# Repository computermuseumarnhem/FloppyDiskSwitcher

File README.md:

# FloppyDiskSwitcher
Select 1 of 4 floppy drives connected to a single controller

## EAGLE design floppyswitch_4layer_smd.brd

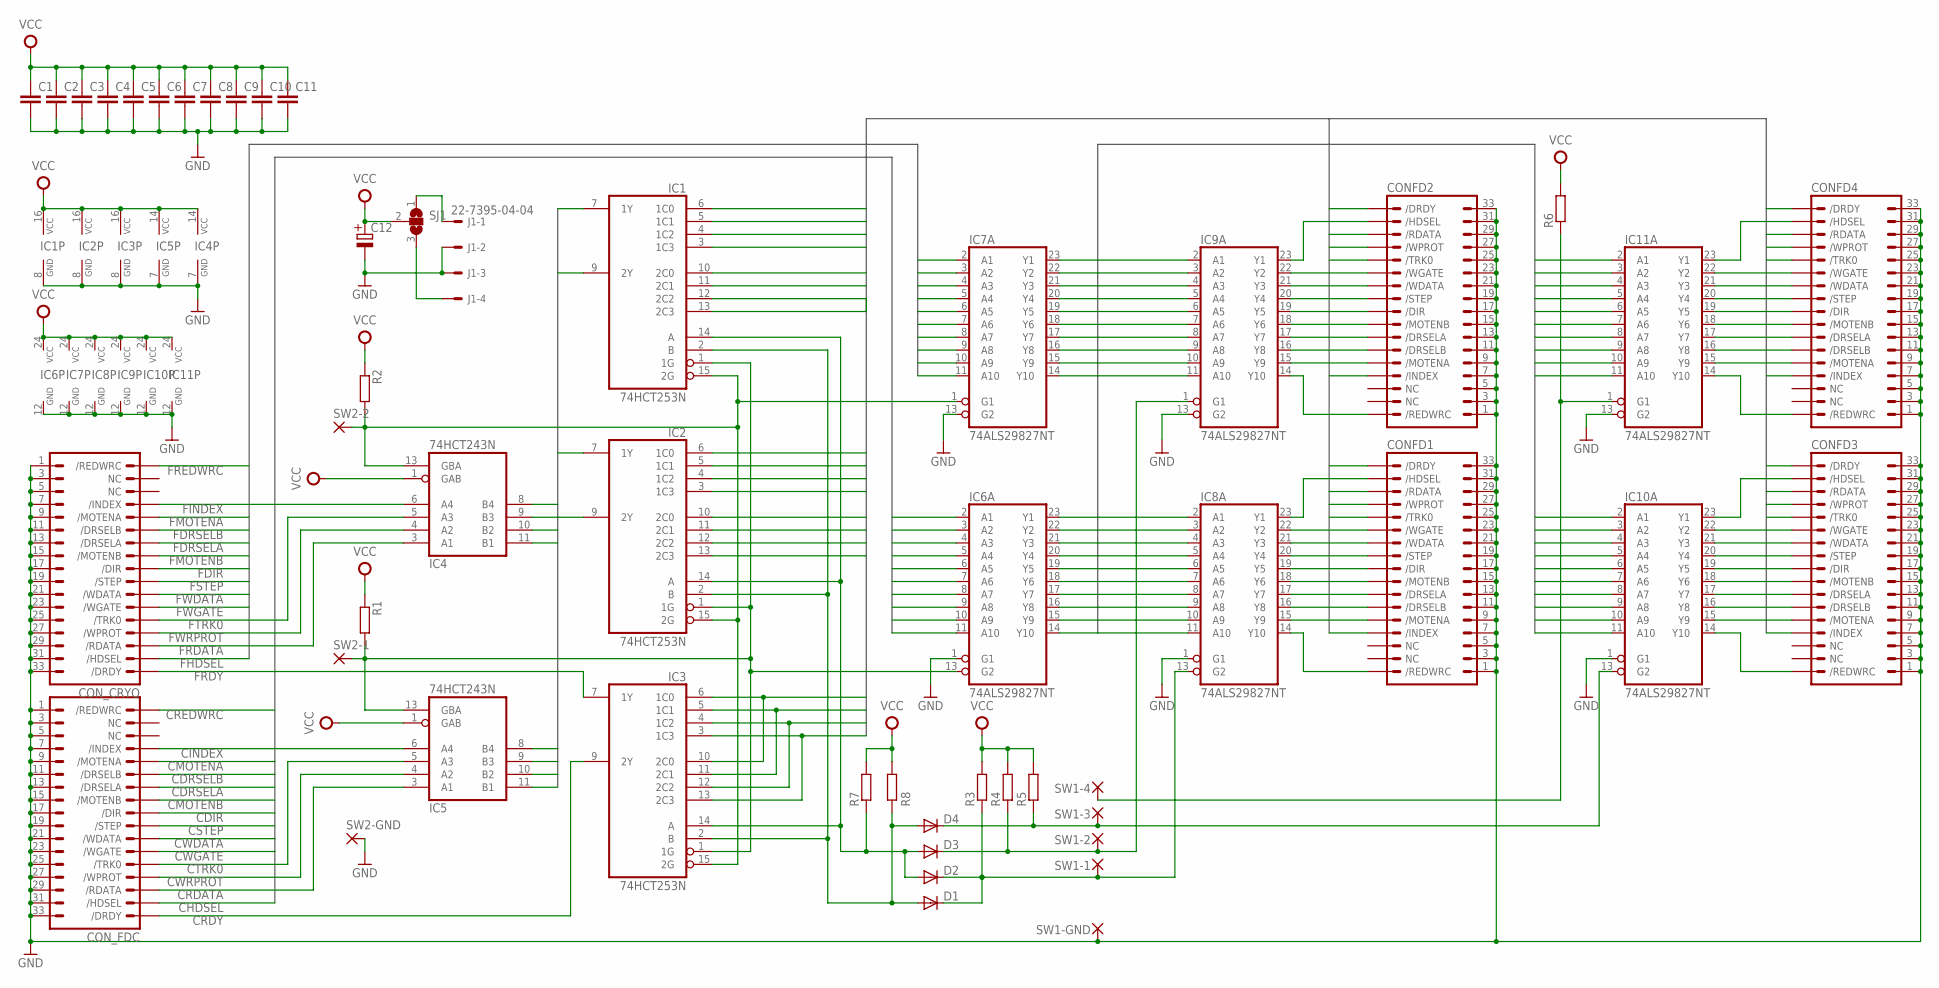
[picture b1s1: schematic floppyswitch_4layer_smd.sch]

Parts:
C1, C5, C6, C7, C8, C9, C10: C-EU075-032X103; C075-032X103
C2: C-EU025-025X050; C025-025X050
C3, C4, C11: C-EU050-025X075; C050-025X075
C12: CPOL-EUE2.5-6; E2,5-6
CONFD1, CONFD2, CONFD3, CONFD4: FDC342X17; 2X17
CON_CRYO: FDC342X17; 2X17
CON_FDC: FDC342X17; 2X17
D1, D2, D3, D4: 1N4148-7; DO35-7
IC1, IC2, IC3: 74HCT253N; DIL16
IC4, IC5: 74HCT243N; DIL14
IC6, IC7, IC8, IC9, IC10, IC11: 74ALS29827NT; SO24W
J1: 22-7395-04-04; 7395-04
R1, R2, R3, R4, R5, R6, R7, R8: R-EU0207/10; 0207/10
SJ1: SJ2W; SJ_2
SW1-1, SW1-2, SW1-3, SW1-4, SW1-GND, SW2-1, SW2-2, SW2-GND: WIREPAD1,6/0,8; 1,6/0,8

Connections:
BUS1: IC6.14 (Y10), IC7.14 (Y10), IC8.11 (A10), IC9.11 (A10), IC10.11 (A10), IC11.11 (A10)
BUS2: IC6.15 (Y9), IC7.15 (Y9), IC8.10 (A9), IC9.10 (A9), IC10.10 (A9), IC11.10 (A9)
BUS3: IC6.16 (Y8), IC7.16 (Y8), IC8.9 (A8), IC9.9 (A8), IC10.9 (A8), IC11.9 (A8)
BUS4: IC6.17 (Y7), IC7.17 (Y7), IC8.8 (A7), IC9.8 (A7), IC10.8 (A7), IC11.8 (A7)
BUS5: IC6.18 (Y6), IC7.18 (Y6), IC8.7 (A6), IC9.7 (A6), IC10.7 (A6), IC11.7 (A6)
BUS6: IC6.19 (Y5), IC7.19 (Y5), IC8.6 (A5), IC9.6 (A5), IC10.6 (A5), IC11.6 (A5)
BUS7: IC6.20 (Y4), IC7.20 (Y4), IC8.5 (A4), IC9.5 (A4), IC10.5 (A4), IC11.5 (A4)
BUS8: IC6.21 (Y3), IC7.21 (Y3), IC8.4 (A3), IC9.4 (A3), IC10.4 (A3), IC11.4 (A3)
BUS9: IC6.22 (Y2), IC7.22 (Y2), IC8.3 (A2), IC9.3 (A2), IC10.3 (A2), IC11.3 (A2)
BUS10: IC6.23 (Y1), IC7.23 (Y1), IC8.2 (A1), IC9.2 (A1), IC10.2 (A1), IC11.2 (A1)
CDIR: CON_FDC.18 (/DIR), IC6.6 (A5)
CDRSELA: CON_FDC.14 (/DRSELA), IC6.8 (A7)
CDRSELB: CON_FDC.12 (/DRSELB), IC6.9 (A8)
CHDSEL: CON_FDC.32 (/HDSEL), IC6.2 (A1)
CINDEX: CON_FDC.8 (/INDEX), IC5.6 (A4)
CMOTENA: CON_FDC.10 (/MOTENA), IC6.10 (A9)
CMOTENB: CON_FDC.16 (/MOTENB), IC6.7 (A6)
CRDATA: CON_FDC.30 (/RDATA), IC5.3 (A1)
CRDY: CON_FDC.34 (/DRDY), IC3.9 (2Y)
CREDWRC: CON_FDC.2 (/REDWRC), IC6.11 (A10)
CSTEP: CON_FDC.20 (/STEP), IC6.5 (A4)
CTRK0: CON_FDC.26 (/TRK0), IC5.5 (A3)
CWDATA: CON_FDC.22 (/WDATA), IC6.4 (A3)
CWGATE: CON_FDC.24 (/WGATE), IC6.3 (A2)
CWRPROT: CON_FDC.28 (/WPROT), IC5.4 (A2)
FDIR: CON_CRYO.18 (/DIR), IC7.6 (A5)
FDRSELA: CON_CRYO.14 (/DRSELA), IC7.8 (A7)
FDRSELB: CON_CRYO.12 (/DRSELB), IC7.9 (A8)
FHDSEL: CON_CRYO.32 (/HDSEL), IC7.2 (A1)
FINDEX: CON_CRYO.8 (/INDEX), IC4.6 (A4)
FMOTENA: CON_CRYO.10 (/MOTENA), IC7.10 (A9)
FMOTENB: CON_CRYO.16 (/MOTENB), IC7.7 (A6)
FRDATA: CON_CRYO.30 (/RDATA), IC4.3 (A1)
FRDY: CON_CRYO.34 (/DRDY), IC3.7 (1Y)
FREDWRC: CON_CRYO.2 (/REDWRC), IC7.11 (A10)
FSTEP: CON_CRYO.20 (/STEP), IC7.5 (A4)
FTRK0: CON_CRYO.26 (/TRK0), IC4.5 (A3)
FWDATA: CON_CRYO.22 (/WDATA), IC7.4 (A3)
FWGATE: CON_CRYO.24 (/WGATE), IC7.3 (A2)
FWRPROT: CON_CRYO.28 (/WPROT), IC4.4 (A2)
GND: C1.2, C2.2, C3.2, C4.2, C5.2, C6.2, C7.2, C8.2, C9.2, C10.2, C11.2, C12.-, CONFD1.1, CONFD1.3, CONFD1.5, CONFD1.7, CONFD1.9, CONFD1.11, CONFD1.13, CONFD1.15, CONFD1.17, CONFD1.19, CONFD1.21, CONFD1.23, CONFD1.25, CONFD1.27, CONFD1.29, CONFD1.31, CONFD1.33, CONFD2.1, CONFD2.3, CONFD2.5, CONFD2.7, CONFD2.9, CONFD2.11, CONFD2.13, CONFD2.15, CONFD2.17, CONFD2.19, CONFD2.21, CONFD2.23, CONFD2.25, CONFD2.27, CONFD2.29, CONFD2.31, CONFD2.33, CONFD3.1, CONFD3.3, CONFD3.5, CONFD3.7, CONFD3.9, CONFD3.11, CONFD3.13, CONFD3.15, CONFD3.17, CONFD3.19, CONFD3.21, CONFD3.23, CONFD3.25, CONFD3.27, CONFD3.29, CONFD3.31, CONFD3.33, CONFD4.1, CONFD4.3, CONFD4.5, CONFD4.7, CONFD4.9, CONFD4.11, CONFD4.13, CONFD4.15, CONFD4.17, CONFD4.19, CONFD4.21, CONFD4.23, CONFD4.25, CONFD4.27, CONFD4.29, CONFD4.31, CONFD4.33, CON_CRYO.1, CON_CRYO.3, CON_CRYO.5, CON_CRYO.7, CON_CRYO.9, CON_CRYO.11, CON_CRYO.13, CON_CRYO.15, CON_CRYO.17, CON_CRYO.19, CON_CRYO.21, CON_CRYO.23, CON_CRYO.25, CON_CRYO.27, CON_CRYO.29, CON_CRYO.31, CON_CRYO.33, CON_FDC.1, CON_FDC.3, CON_FDC.5, CON_FDC.7, CON_FDC.9, CON_FDC.11, CON_FDC.13, CON_FDC.15, CON_FDC.17, CON_FDC.19, CON_FDC.21, CON_FDC.23, CON_FDC.25, CON_FDC.27, CON_FDC.29, CON_FDC.31, CON_FDC.33, IC1.8 (GND), IC2.8 (GND), IC3.8 (GND), IC4.7 (GND), IC5.7 (GND), IC6.1 (G1), IC6.12 (GND), IC7.12 (GND), IC7.13 (G2), IC8.1 (G1), IC8.12 (GND), IC9.12 (GND), IC9.13 (G2), IC10.1 (G1), IC10.12 (GND), IC11.12 (GND), IC11.13 (G2), J1.2, J1.3, SW1-GND.1, SW2-GND.1
INDEX: IC1.7 (1Y), IC4.8 (B4), IC5.8 (B4)
INDEX1: CONFD1.8 (/INDEX), IC1.6 (1C0)
INDEX2: CONFD2.8 (/INDEX), IC1.5 (1C1)
INDEX3: CONFD3.8 (/INDEX), IC1.4 (1C2)
INDEX4: CONFD4.8 (/INDEX), IC1.3 (1C3)
unnamed: CONFD2.10 (/MOTENA), IC9.15 (Y9)
unnamed: CONFD2.12 (/DRSELB), IC9.16 (Y8)
unnamed: CONFD2.14 (/DRSELA), IC9.17 (Y7)
unnamed: CONFD2.16 (/MOTENB), IC9.18 (Y6)
unnamed: CONFD2.18 (/DIR), IC9.19 (Y5)
unnamed: CONFD2.20 (/STEP), IC9.20 (Y4)
unnamed: CONFD2.22 (/WDATA), IC9.21 (Y3)
unnamed: CONFD2.24 (/WGATE), IC9.22 (Y2)
unnamed: CONFD2.32 (/HDSEL), IC9.23 (Y1)
unnamed: CONFD2.2 (/REDWRC), IC9.14 (Y10)
unnamed: CONFD1.24 (/WGATE), IC8.22 (Y2)
unnamed: CONFD1.22 (/WDATA), IC8.21 (Y3)
unnamed: CONFD1.20 (/STEP), IC8.20 (Y4)
unnamed: CONFD1.18 (/DIR), IC8.19 (Y5)
unnamed: CONFD1.16 (/MOTENB), IC8.18 (Y6)
unnamed: CONFD1.14 (/DRSELA), IC8.17 (Y7)
unnamed: CONFD1.12 (/DRSELB), IC8.16 (Y8)
unnamed: IC1.1 (1G), IC2.1 (1G), IC3.1 (1G), IC5.13 (GBA), IC6.13 (G2), R1.2, SW2-1.1
unnamed: CONFD1.10 (/MOTENA), IC8.15 (Y9)
unnamed: CONFD1.2 (/REDWRC), IC8.14 (Y10)
unnamed: CONFD1.32 (/HDSEL), IC8.23 (Y1)
unnamed: CONFD3.32 (/HDSEL), IC10.23 (Y1)
unnamed: CONFD3.24 (/WGATE), IC10.22 (Y2)
unnamed: CONFD3.22 (/WDATA), IC10.21 (Y3)
unnamed: CONFD3.20 (/STEP), IC10.20 (Y4)
unnamed: CONFD3.18 (/DIR), IC10.19 (Y5)
unnamed: CONFD3.16 (/MOTENB), IC10.18 (Y6)
unnamed: CONFD3.14 (/DRSELA), IC10.17 (Y7)
unnamed: CONFD3.12 (/DRSELB), IC10.16 (Y8)
unnamed: CONFD3.10 (/MOTENA), IC10.15 (Y9)
unnamed: CONFD3.2 (/REDWRC), IC10.14 (Y10)
unnamed: CONFD4.24 (/WGATE), IC11.22 (Y2)
unnamed: CONFD4.22 (/WDATA), IC11.21 (Y3)
unnamed: CONFD4.20 (/STEP), IC11.20 (Y4)
unnamed: CONFD4.18 (/DIR), IC11.19 (Y5)
unnamed: CONFD4.16 (/MOTENB), IC11.18 (Y6)
unnamed: CONFD4.14 (/DRSELA), IC11.17 (Y7)
unnamed: CONFD4.12 (/DRSELB), IC11.16 (Y8)
unnamed: CONFD4.10 (/MOTENA), IC11.15 (Y9)
unnamed: CONFD4.2 (/REDWRC), IC11.14 (Y10)
unnamed: CONFD4.32 (/HDSEL), IC11.23 (Y1)
unnamed: IC1.15 (2G), IC2.15 (2G), IC3.15 (2G), IC4.13 (GBA), IC7.1 (G1), R2.2, SW2-2.1
unnamed: D3.C, IC9.1 (G1), R4.1, SW1-2.1
unnamed: J1.4, SJ1.3
unnamed: IC11.1 (G1), R6.1, SW1-4.1
unnamed: D4.C, IC10.13 (G2), R5.1, SW1-3.1
unnamed: D2.A, D3.A, IC1.14 (A), IC2.14 (A), IC3.14 (A), R7.1
unnamed: D1.A, D4.A, IC1.2 (B), IC2.2 (B), IC3.2 (B), R8.1
unnamed: J1.1, SJ1.1
unnamed: D1.C, D2.C, IC8.13 (G2), R3.1, SW1-1.1
RDATA: IC2.9 (2Y), IC4.11 (B1), IC5.11 (B1)
RDATA1: CONFD1.30 (/RDATA), IC2.10 (2C0)
RDATA2: CONFD2.30 (/RDATA), IC2.11 (2C1)
RDATA3: CONFD3.30 (/RDATA), IC2.12 (2C2)
RDATA4: CONFD4.30 (/RDATA), IC2.13 (2C3)
RDY1: CONFD1.34 (/DRDY), IC3.6 (1C0), IC3.10 (2C0)
RDY2: CONFD2.34 (/DRDY), IC3.5 (1C1), IC3.11 (2C1)
RDY3: CONFD3.34 (/DRDY), IC3.4 (1C2), IC3.12 (2C2)
RDY4: CONFD4.34 (/DRDY), IC3.3 (1C3), IC3.13 (2C3)
TRK0: IC1.9 (2Y), IC4.9 (B3), IC5.9 (B3)
TRKZ1: CONFD1.26 (/TRK0), IC1.10 (2C0)
TRKZ2: CONFD2.26 (/TRK0), IC1.11 (2C1)
TRKZ3: CONFD3.26 (/TRK0), IC1.12 (2C2)
TRKZ4: CONFD4.26 (/TRK0), IC1.13 (2C3)
VCC: C1.1, C2.1, C3.1, C4.1, C5.1, C6.1, C7.1, C8.1, C9.1, C10.1, C11.1, C12.+, IC1.16 (VCC), IC2.16 (VCC), IC3.16 (VCC), IC4.1 (GAB), IC4.14 (VCC), IC5.1 (GAB), IC5.14 (VCC), IC6.24 (VCC), IC7.24 (VCC), IC8.24 (VCC), IC9.24 (VCC), IC10.24 (VCC), IC11.24 (VCC), R1.1, R2.1, R3.2, R4.2, R5.2, R6.2, R7.2, R8.2, SJ1.2
WRPROT: IC2.7 (1Y), IC4.10 (B2), IC5.10 (B2)
WRPROT1: CONFD1.28 (/WPROT), IC2.6 (1C0)
WRPROT2: CONFD2.28 (/WPROT), IC2.5 (1C1)
WRPROT3: CONFD3.28 (/WPROT), IC2.4 (1C2)
WRPROT4: CONFD4.28 (/WPROT), IC2.3 (1C3)

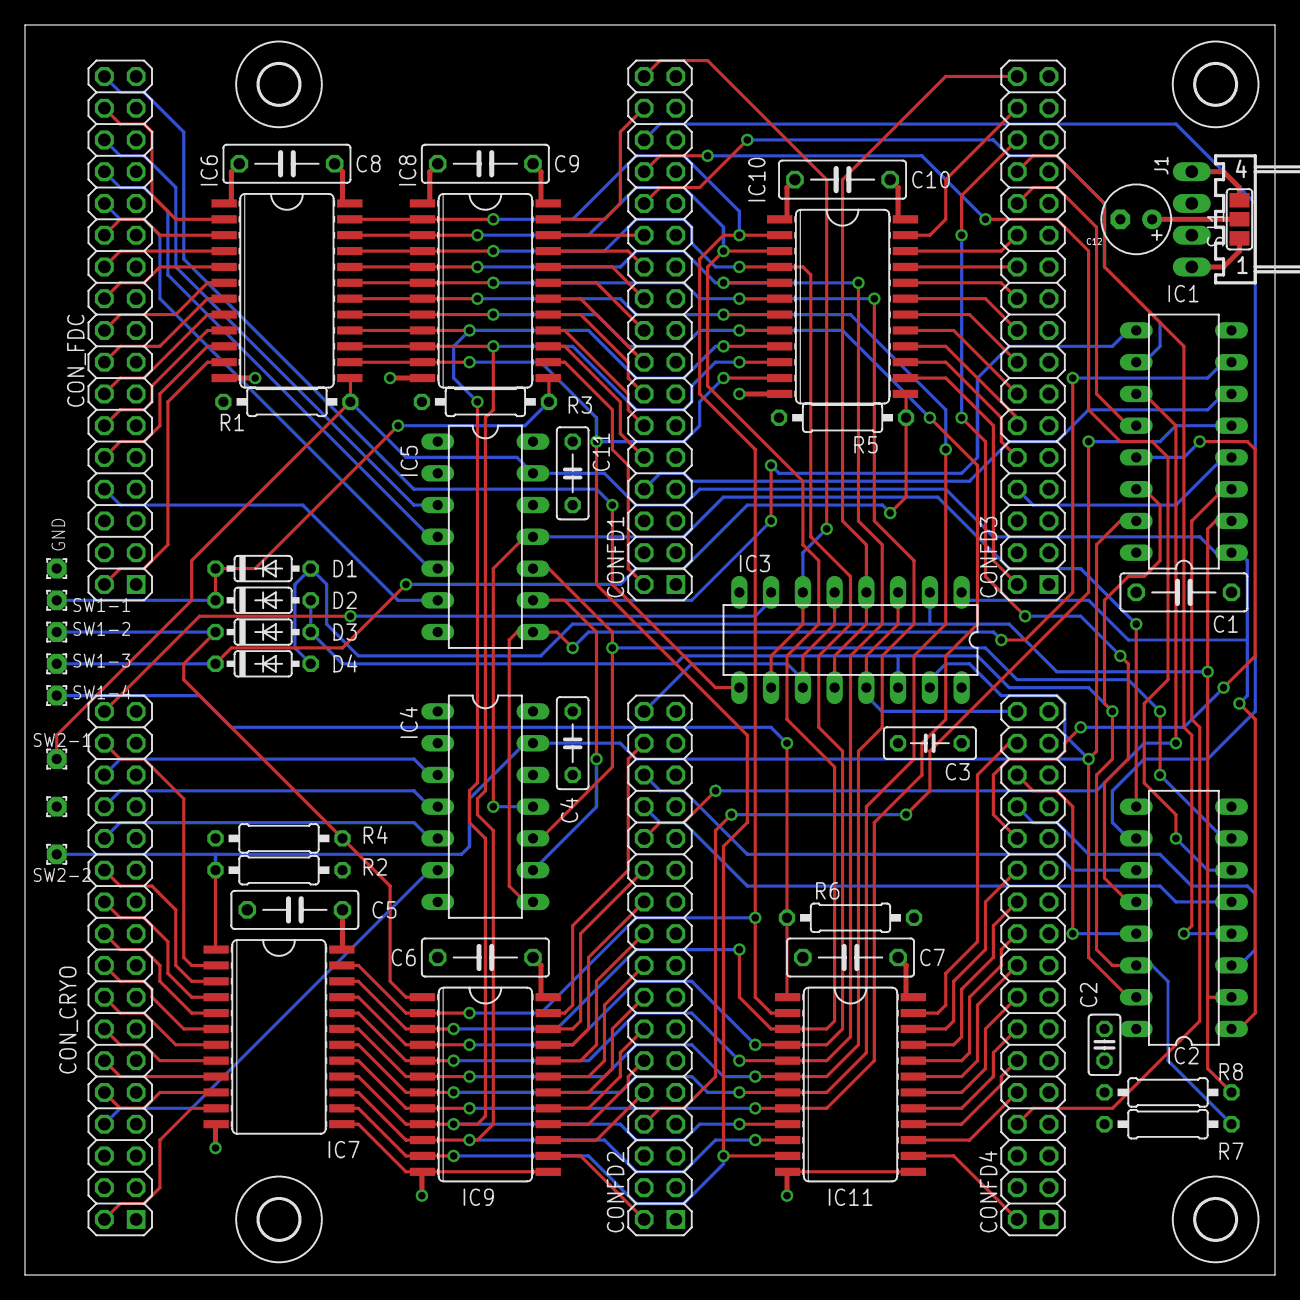
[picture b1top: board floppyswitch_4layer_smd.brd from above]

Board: 4 copper layers, 100.0 x 100.0 mm, 55 parts (0 on the bottom side), 116 nets.

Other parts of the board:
U$1, U$2, U$3, U$4: 3,2

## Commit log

2021-03-08 EAGLE files and Gerbers
